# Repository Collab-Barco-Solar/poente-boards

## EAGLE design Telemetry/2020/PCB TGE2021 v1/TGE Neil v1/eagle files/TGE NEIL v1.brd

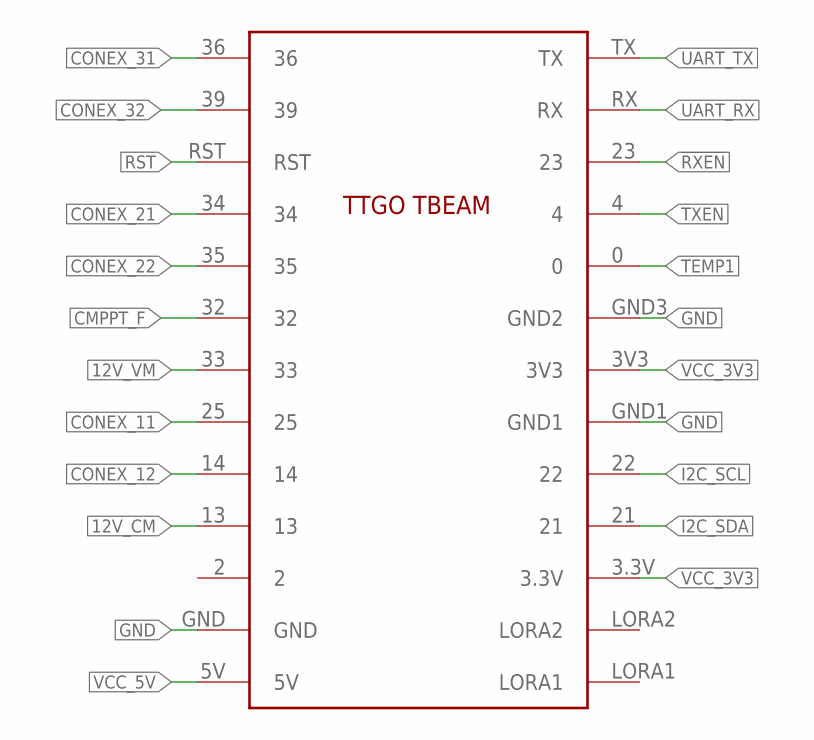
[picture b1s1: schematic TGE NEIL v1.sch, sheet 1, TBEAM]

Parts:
U$1: TTGOBEAM

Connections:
12V_CM: U$1.13; also elsewhere on the board
12V_VM: U$1.33; also elsewhere on the board
!RXEN: U$1.23; also elsewhere on the board
CMPPT_F: U$1.32; also elsewhere on the board
CONEX_11: U$1.25; also elsewhere on the board
CONEX_12: U$1.14; also elsewhere on the board
CONEX_21: U$1.34; also elsewhere on the board
CONEX_22: U$1.35; also elsewhere on the board
CONEX_31: U$1.36; also elsewhere on the board
CONEX_32: U$1.39; also elsewhere on the board
GND: U$1.GND, U$1.GND1, U$1.GND3 (GND2); also elsewhere on the board
I2C_SCL: U$1.22; also elsewhere on the board
I2C_SDA: U$1.21; also elsewhere on the board
RST: U$1.RST
TEMP1: U$1.0; also elsewhere on the board
TXEN: U$1.4; also elsewhere on the board
UART_RX: U$1.RX; also elsewhere on the board
UART_TX: U$1.TX; also elsewhere on the board
VCC_3V3: U$1.3.3V, U$1.3V3; also elsewhere on the board
VCC_5V: U$1.5V; also elsewhere on the board

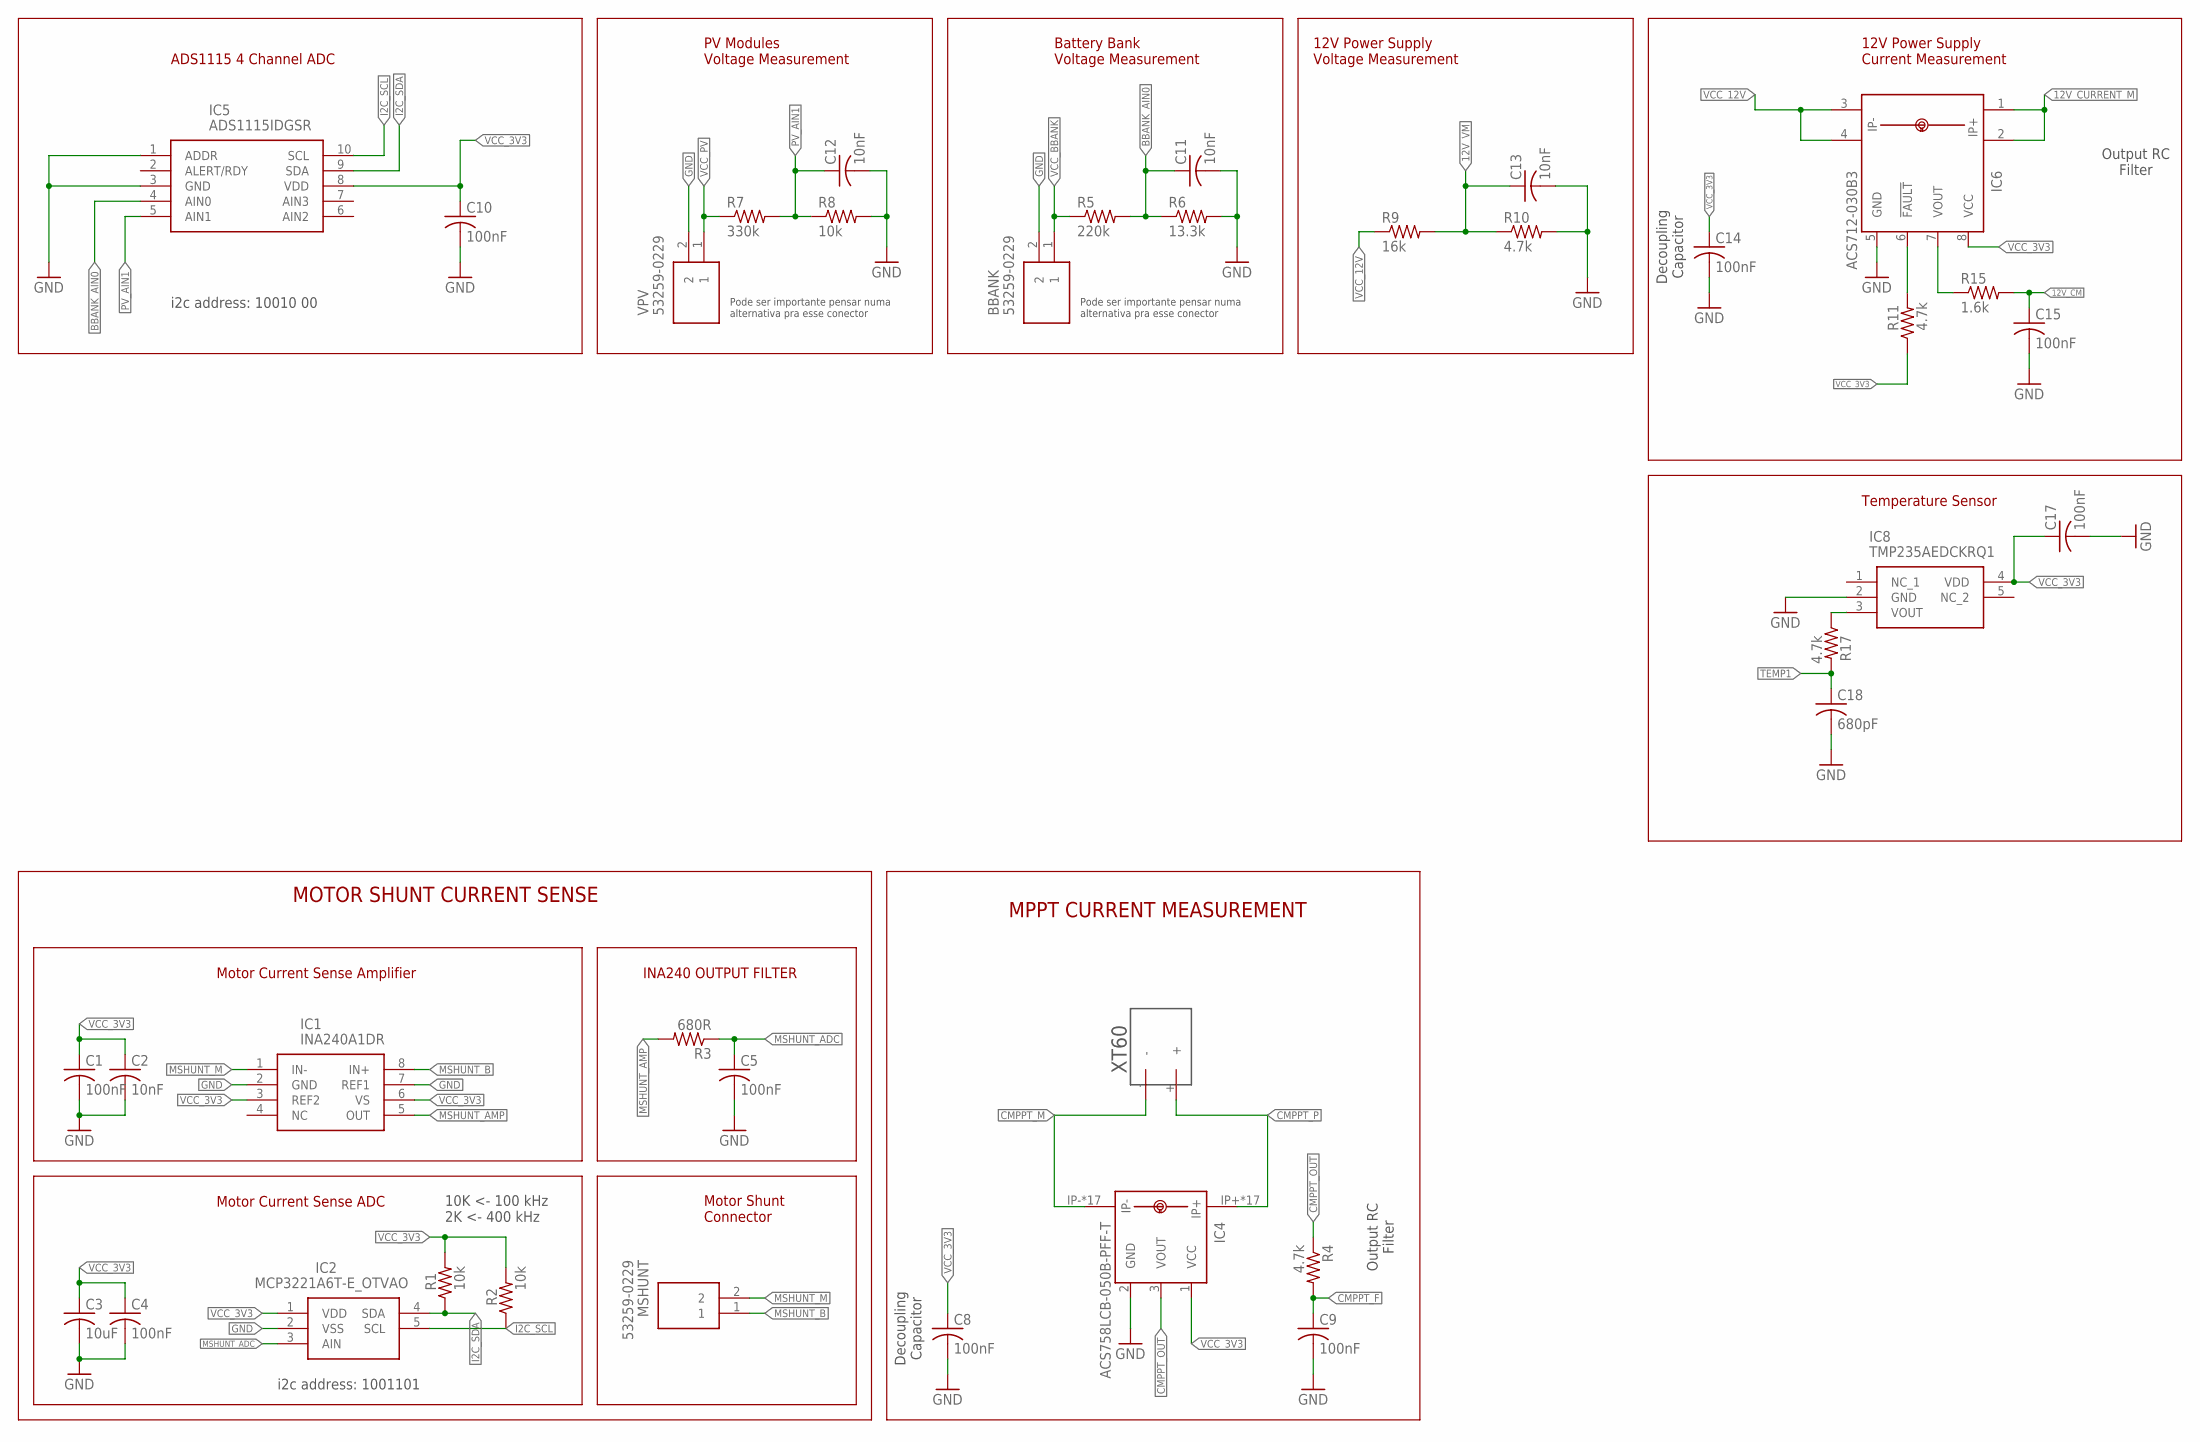
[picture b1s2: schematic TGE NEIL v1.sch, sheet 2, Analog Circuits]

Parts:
BBANK: 53259-0229; 0532590229
C1, C4, C5, C8, C9, C10, C14, C15, C17: 100nF; C0805
C2, C11, C12, C13: 10nF; C0805
C3: 10uF; C0805
C18: 680pF; C0805
IC1: INA240A1DR; SOIC127P600X175-8N
IC2: MCP3221A6T-E_OTVAO; SOT95P280X145-5N
IC4: ACS758LCB-050B-PFF-T; CB-PFF
IC5: ADS1115IDGSR; SOP50P490X110-10N
IC6: ACS712-030B3; SOIC8
IC8: TMP235AEDCKRQ1; SOT65P210X110-5N
MSHUNT: 53259-0229; 0532590229
R1, R2, R8: 10k; R0805
R3: 680R; R0805
R4, R10, R11, R17: 4.7k; R0805
R5: 220k; R0805
R6: 13.3k; R0805
R7: 330k; R0805
R9: 16k; R0805
R15: 1.6k; R0805
U$3: XT60
VPV: 53259-0229; 0532590229

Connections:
12V_CM: C15.1, R15.2; also elsewhere on the board
12V_CURRENT_M: IC6.1 (IP+), IC6.2 (IP+1); also elsewhere on the board
12V_VM: C13.1, R9.2, R10.1; also elsewhere on the board
BBANK_AIN0: C11.1, IC5.4 (AIN0), R5.2, R6.1
CMPPT_F: C9.1, R4.2; also elsewhere on the board
CMPPT_M: IC4.IP-, IC4.IP-@2 (IP-), IC4.IP-@3 (IP-), IC4.IP-@4 (IP-), IC4.IP-@5 (IP-), IC4.IP-@6 (IP-), IC4.IP-@7 (IP-), IC4.IP-@8 (IP-), IC4.IP-@9 (IP-), IC4.IP-@10 (IP-), IC4.IP-@11 (IP-), IC4.IP-@12 (IP-), IC4.IP-@13 (IP-), IC4.IP-@14 (IP-), IC4.IP-@15 (IP-), IC4.IP-@16 (IP-), IC4.IP-@17 (IP-), U$3.-
CMPPT_OUT: IC4.3 (VOUT), R4.1
CMPPT_P: IC4.IP+, IC4.IP+@2 (IP+), IC4.IP+@3 (IP+), IC4.IP+@4 (IP+), IC4.IP+@5 (IP+), IC4.IP+@6 (IP+), IC4.IP+@7 (IP+), IC4.IP+@8 (IP+), IC4.IP+@9 (IP+), IC4.IP+@10 (IP+), IC4.IP+@11 (IP+), IC4.IP+@12 (IP+), IC4.IP+@13 (IP+), IC4.IP+@14 (IP+), IC4.IP+@15 (IP+), IC4.IP+@16 (IP+), IC4.IP+@17 (IP+), U$3.+
GND: BBANK.2, C1.2, C2.2, C3.2, C4.2, C5.2, C8.2, C9.2, C10.2, C11.2, C12.2, C13.2, C14.2, C15.2, C17.2, C18.2, IC1.2 (GND), IC1.7 (REF1), IC2.2 (VSS), IC4.2 (GND), IC5.1 (ADDR), IC5.3 (GND), IC6.5 (GND), IC8.2 (GND), R6.2, R8.2, R10.2, VPV.2; also elsewhere on the board
I2C_SCL: IC2.5 (SCL), IC5.10 (SCL), R2.1; also elsewhere on the board
I2C_SDA: IC2.4 (SDA), IC5.9 (SDA), R1.1; also elsewhere on the board
MSHUNT_ADC: C5.1, IC2.3 (AIN), R3.1
MSHUNT_AMP: IC1.5 (OUT), R3.2
MSHUNT_B: IC1.8 (IN+), MSHUNT.1
MSHUNT_M: IC1.1 (IN-), MSHUNT.2
unnamed: IC6.6 (!FAULT), R11.2
unnamed: IC6.7 (VOUT), R15.1
unnamed: IC8.3 (VOUT), R17.1
PV_AIN1: C12.1, IC5.5 (AIN1), R7.2, R8.1
TEMP1: C18.1, R17.2; also elsewhere on the board
VCC_3V3: C1.1, C2.1, C3.1, C4.1, C8.1, C10.1, C14.1, C17.1, IC1.3 (REF2), IC1.6 (VS), IC2.1 (VDD), IC4.1 (VCC), IC5.8 (VDD), IC6.8 (VCC), IC8.4 (VDD), R1.2, R2.2, R11.1; also elsewhere on the board
VCC_12V: IC6.3 (IP-), IC6.4 (IP-1), R9.1; also elsewhere on the board
VCC_BBANK: BBANK.1, R5.1
VCC_PV: R7.1, VPV.1

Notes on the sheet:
MOTOR SHUNT CURRENT SENSE
Motor Current Sense Amplifier
Motor Current Sense ADC
Motor Shunt Connector
10K <- 100 kHz 2K <- 400 kHz
i2c address: 1001101
INA240 OUTPUT FILTER
Decoupling Capacitor
MPPT CURRENT MEASUREMENT
Output RC Filter
ADS1115 4 Channel ADC
i2c address: 10010 00
Pode ser importante pensar numa alternativa pra esse conector
Battery Bank Voltage Measurement
PV Modules Voltage Measurement
12V Power Supply Voltage Measurement
12V Power Supply Current Measurement
Temperature Sensor

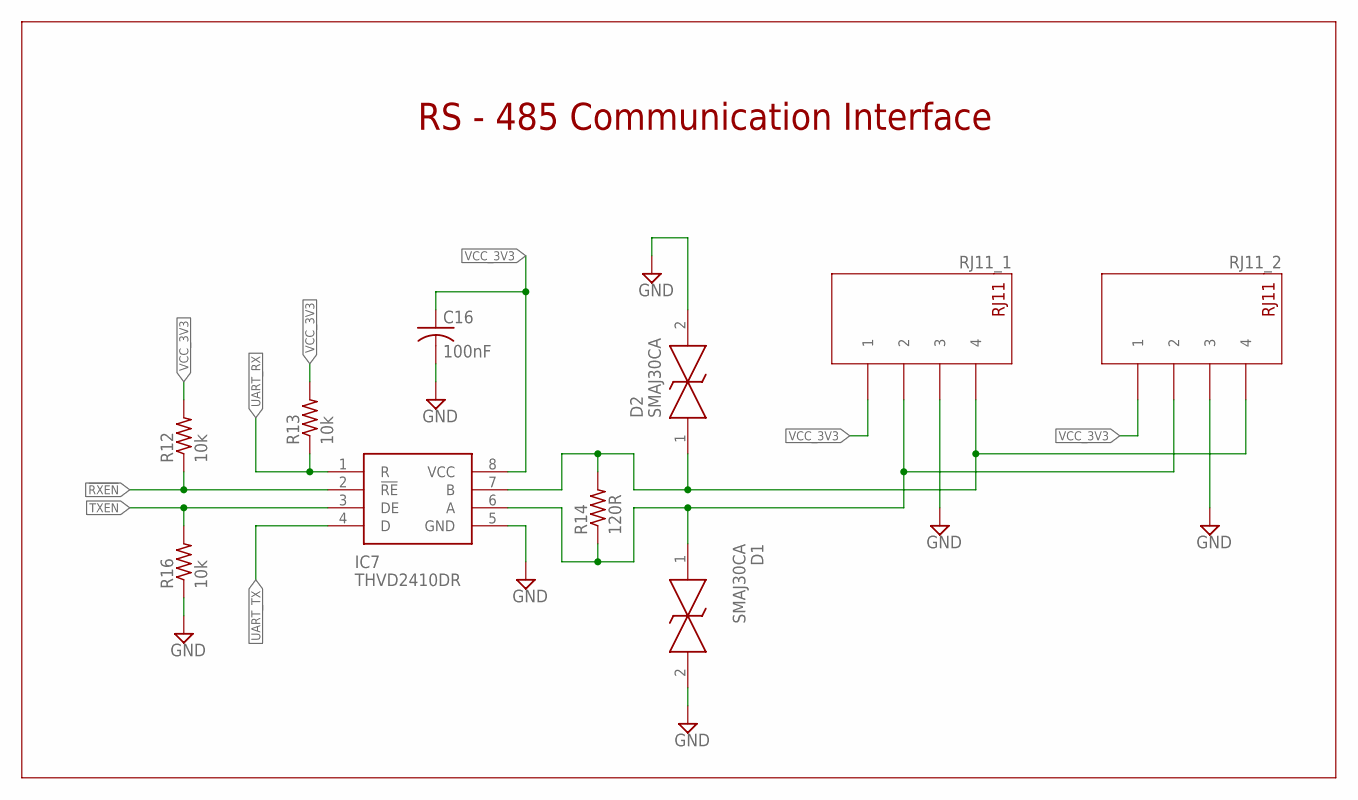
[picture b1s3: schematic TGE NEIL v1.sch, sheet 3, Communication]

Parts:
C16: 100nF; C0805
D1, D2: SMAJ30CA; DIONM5026X229N
IC7: THVD2410DR; SOIC127P600X175-8N
R12, R13, R16: 10k; M0805
R14: 120R; M0805
RJ11_1, RJ11_2: TFC44

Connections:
!RXEN: IC7.2 (!RE), R12.1; also elsewhere on the board
GND: C16.2, D1.2, D2.2, IC7.5 (GND), R16.1, RJ11_1.P$3 (3), RJ11_2.P$3 (3); also elsewhere on the board
RS485_A: D1.1, IC7.6 (A), R14.1, RJ11_1.P$2 (2), RJ11_2.P$2 (2)
RS485_B: D2.1, IC7.7 (B), R14.2, RJ11_1.P$4 (4), RJ11_2.P$4 (4)
TXEN: IC7.3 (DE), R16.2; also elsewhere on the board
UART_RX: IC7.1 (R), R13.1; also elsewhere on the board
UART_TX: IC7.4 (D); also elsewhere on the board
VCC_3V3: C16.1, IC7.8 (VCC), R12.2, R13.2, RJ11_1.P$1 (1), RJ11_2.P$1 (1); also elsewhere on the board

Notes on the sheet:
RS - 485 Communication Interface

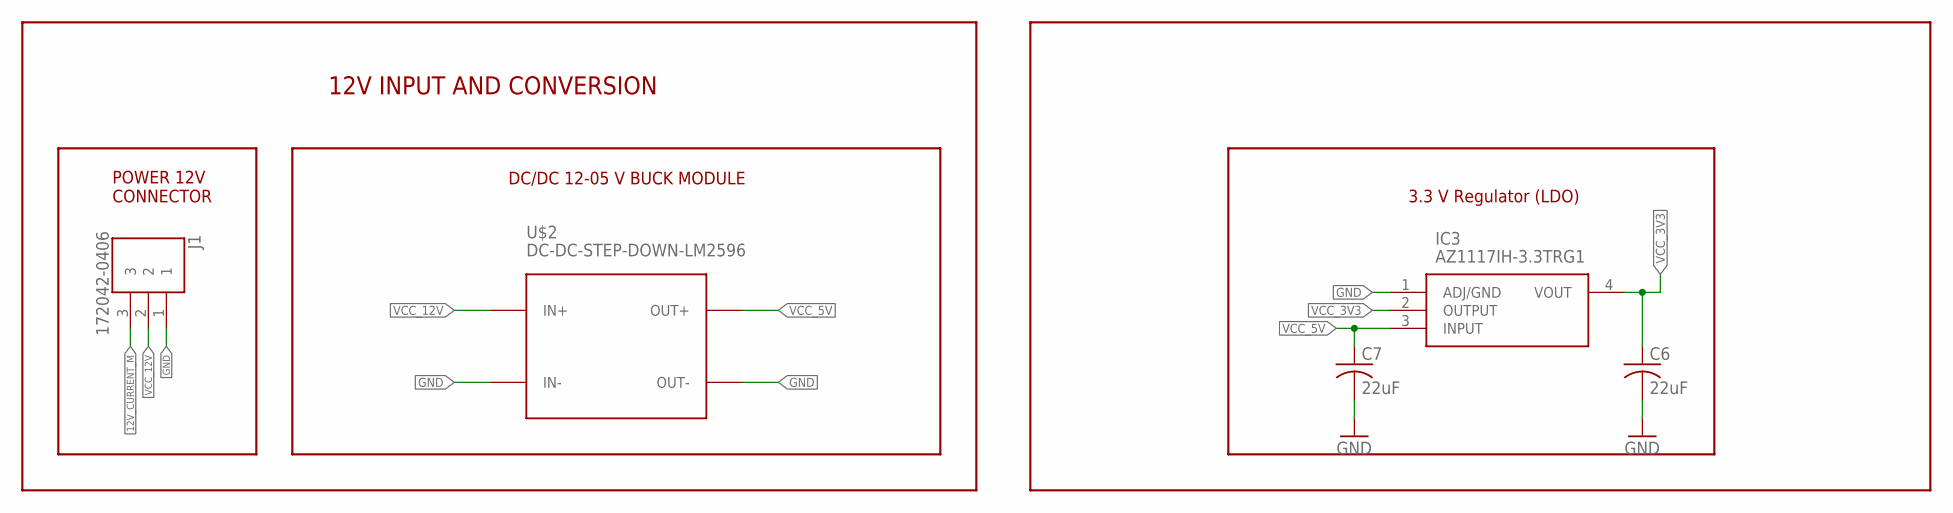
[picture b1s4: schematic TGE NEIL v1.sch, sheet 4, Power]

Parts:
C6, C7: 22uF; C0805
IC3: AZ1117IH-3.3TRG1; SOT230P700X170-4N
J1: 172042-0406; MOLEX_172042-0406
U$2: DC-DC-STEP-DOWN-LM2596

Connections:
12V_CURRENT_M: J1.3; also elsewhere on the board
GND: C6.2, C7.2, IC3.1 (ADJ/GND), J1.1, U$2.IN-, U$2.OUT-; also elsewhere on the board
VCC_3V3: C6.1, IC3.2 (OUTPUT), IC3.4 (VOUT); also elsewhere on the board
VCC_5V: C7.1, IC3.3 (INPUT), U$2.OUT+; also elsewhere on the board
VCC_12V: J1.2, U$2.IN+; also elsewhere on the board

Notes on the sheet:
DC/DC 12-05 V BUCK MODULE
POWER 12V CONNECTOR
12V INPUT AND CONVERSION
3.3 V Regulator (LDO)

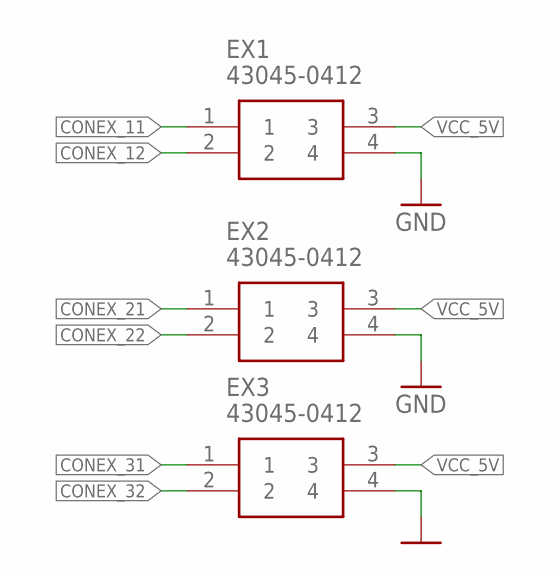
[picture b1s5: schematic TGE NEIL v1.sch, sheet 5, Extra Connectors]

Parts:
EX1, EX2, EX3: 43045-0412

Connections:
CONEX_11: EX1.1; also elsewhere on the board
CONEX_12: EX1.2; also elsewhere on the board
CONEX_21: EX2.1; also elsewhere on the board
CONEX_22: EX2.2; also elsewhere on the board
CONEX_31: EX3.1; also elsewhere on the board
CONEX_32: EX3.2; also elsewhere on the board
GND: EX1.4, EX2.4, EX3.4; also elsewhere on the board
VCC_5V: EX1.3, EX2.3, EX3.3; also elsewhere on the board

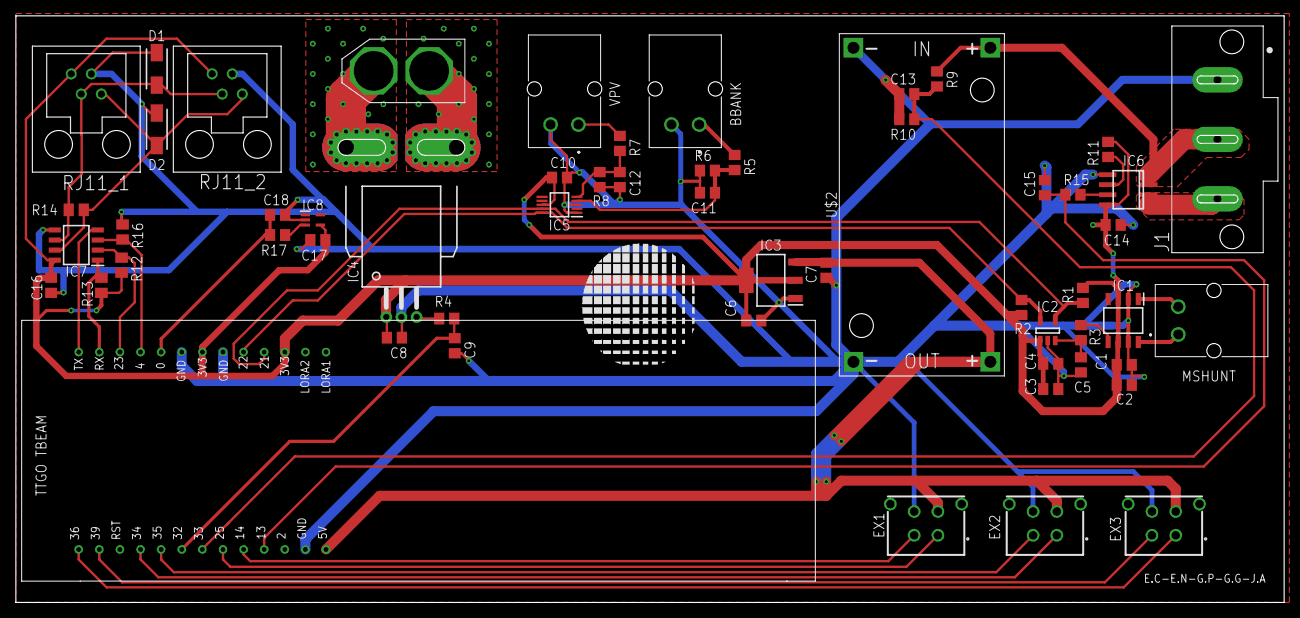
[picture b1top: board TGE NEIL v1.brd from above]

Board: 2 copper layers, 160.0 x 74.0 mm, 57 parts (0 on the bottom side), 37 nets.

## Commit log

2020-02-17 Inicializei o repositório e deixei o que era relevante no escopo
    Removi os arquivos que não faziam parte do circuito ou placa
2020-07-26 2019 e 2020 separeted
    Inicio do circuito de 2020 (MSHUNT) separacao do que foi feito em 2019
2020-08-02 Att shunt measure and organizing folders
    Some folders organized and RC filter added to the motor shunt measure
2020-08-02 HighLight in DCDC guide document
2020-08-02 Begining of 3V3 Regulator Circuit
    LDO AZ111 added to the circuit. The input filter is under research.
2020-08-08 Adding Filtering article and removing non used files
    Article about using LDO as a filter.
2020-08-08 apenas corrigi o valor de um capacitor
2020-08-12 Pasta do circuito LDO
2020-08-12 ABOUT LDO: TIDA-013222 Ref. Design
    Adding the schematic and pcb layour of a texas reference design for LDO application
2020-08-12 Summary of LDO use document
2020-08-12 Ajustes de posicionamento no sch e brd
2020-08-13 Hall effect current sensors material
    Some datasheets and a nice small article
2020-08-13 Renaming motor shunt signals
    i had named the shunt signals with the sufix _N and _P but this is understood as differential signals on eagle.
2020-08-16 SAR ADC's input circuits recommendation
    Documents about use of sar ADC's with RC filters and/or high impedance input.
2020-08-16 Adding ACD758 datasheet to the library
2020-08-16 Adding Allegro 2 library and LM2596 3D part
2020-08-16 Positioning parts on pcb for preview in fusion
2020-08-16 Starting ACS758 circuit.
2020-08-16 Correcting a title mistake
2020-08-16 Organizing datasheet folder
2020-08-17 Organizing folder structure - Base Material
    Now the base material folder will be separeted by circuits.
2020-08-17 Create Circuit_Projec_Notes.md
    Initializing project notes
2020-08-17 Update Circuit_Projec_Notes.md
    Nothing capital
2020-08-17 Starting introduction
2020-08-17 Adding link
2020-08-17 correcting link
2020-08-17 correcting link message
2020-08-17 Output filters impedance
2020-08-17 Organizing MCU informations Folder
2020-08-17 Adding ACS infos to the document
2020-08-20 Filter Definition section added to the document
    Definition of the RC filter values
2020-08-20 MPPT Current: Organizing and adding filter
    Sch. now with a better look, RC filter and decoupling capacitor with values.
2020-08-20 Just updating past commit (MPPT current measurement)
2020-08-20 Removing autosave files
2020-08-20 Correcting a mistake in the text
2020-08-20 Improving writing
2020-08-21 Adding a connector to mppt current sense
2020-08-22 Adding XT60 documents
2020-08-22 XT60 changes
2020-08-22 Starting PCB design tips section
2020-08-22 Adding Current Input Traces an planes.
2020-08-22 Position updates to the board.
2020-08-22 correcting grammatical error
2020-08-23 Adding Assembly Guide and organizing documents
2020-08-23 just moved the LDO (not importante by now)
2020-08-23 Highlights on document SAR ADC without amp.
2020-08-23 more material about sar adcs.
2020-08-27 Adding simplified simulation adcs and adc cookbook AN
2020-08-27 Adding reading highlights
2020-08-27 some more highlights
2020-08-29 Adding ADS115 datasheet
2020-08-30 Simulation: Input Interface V_batt_bank
2020-08-30 adding notes at ads1115 datasheet
2020-08-30 Adding OPAMP with gain one
2020-08-30 improving the analisis
2020-08-30 removing simulation resusts leaving just the sch.
2020-08-30 Adding ADS1115 and BBank input circuit
2020-08-30 Some new datasheet highlights
2020-08-31 Adding the initial sch. of the PV voltage measurement circuit
2020-09-04 MPPT Current sense simulation
2020-09-04 Addin motor current measurement simulation circuit
2020-09-07 Organizing Poent-boards branch
2020-10-22 Correcting an circuit name
2020-10-26 Adding voltage and current measurements for the 12V Power Supply
2020-10-26 corrigindo esquematico
2020-10-26 adicionando novos circuitos a placa
2020-10-27 Adicao do documento de instrucoes e organizacao das pastas.
2020-10-27 Corrigindo formatacao
2020-10-27 Correção de algumas palavras e frases
2020-10-29 correcao no valor de resistores - circuito medicao de tensao 12 V
2020-10-30 Edição para referenciar os pinos I/O e mudar modelo do sensor
2020-10-30 Referência dos pinos I/O e troca do modelo do Sensor Hall
    Os pinos a serem utilizados para a medição de tensão e corrente estão nomeados como ADC1_4 e ADC1_5 respectivamente, sendo eles os pinos 32 e 33 do TTGO-TBEAM. O Sensor Hall foi trocado para o modelo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
2020-10-30 Atualizando para o modelo correto do Sensor Hall
2020-11-01 correcting circuit errors
2020-11-01 Correcao no circuito de medicao de corrente, adicao de conectores e simulacao da medicao de corrente
2020-11-05 Uploading datasheets and overviews about RS485
2020-11-06 adicionando datasheets
2020-11-07 documento comparando os transceivers
2020-11-07 grifando partes de alguns pdfs rs485
2020-11-09 adicao de novos materiais sober o RS-485
2020-11-09 Esquematico RS485
2020-11-12 Editing files and uploading TMP100 datasheet
2020-11-12 Adding temperature sensor TMP100
2020-11-12 Adjusting folder's name
2020-11-14 Uploading temperature sensors datasheets
2020-11-14 adicao de conectores extras para testes e datasheets dos sensores de temperaetura
2020-11-14 adicionando comparacao entre sensores de temperatura
2020-11-14 adicao de datasheets e modificacoes no documento de comparacao
2020-11-14 Adicao do sensor de temperetura ao esquemático
2020-11-16 "Editing" commit
2020-11-16 Uploading TMP235 wiring
    Extra connectors without wiring, that's the reason for V1.07.01
2020-11-16 ajustes versao 1.07
2020-11-16 adicionando novo conector
2020-11-17 "Editing" commit for final version 1.07
2020-11-17 Final v1.07
    Final version with extra connectors and temperature sensor wired properly
2020-11-17 removendo arquivo autosave
2020-11-18 coisas que fizemos durante a reuniao 18/11
2020-11-20 WIP commit
2020-11-23 WIP PCB
2020-11-23 criacao de nova versao de roteamento
2020-11-24 primeira versao de roteamento - carece de revisão
2020-11-28 corrigindo sinais scl e sda I2C
2021-03-01 organizacao de arquivos e exclusao de auto-saves
2021-08-27 atualizacao da versao da placa

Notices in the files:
parts and their libraries:
diy-modules: Released under the Creative Commons Attribution 4.0 International License: http://creativecommons.org/licenses/by/4.0
